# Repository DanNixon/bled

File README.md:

<h1 align="center">BLED</h1>

<p align="center">
  Versatile control board for WS2812 compatible LED fixtures.
  Using WebAssembly for effects and Bluetooth Low Energy for control.
</p>

---

**BLED is a work in progress.** Although mostly feature complete, specifics of the effect API are subject to change.
The web UI is likely to undergo significant changes, the current version is a mostly vibe coded prototype.

Documentation can be found in [`docs/README.md`](docs/README.md).

## Building effects

[`bled-effect`](lib/effect/README.md) is a helper library for building BLED effects in Rust and compiling them to WebAssembly. The [`effects`](effects) directory contains example effect crates.

## License

The project is licensed under the MIT License, see [`LICENSE.txt`](LICENSE.txt).

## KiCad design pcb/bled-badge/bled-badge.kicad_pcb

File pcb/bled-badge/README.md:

# Badge LED panel

A badge sized LED panel that takes a [BLED Stamp](../bled-stamp).

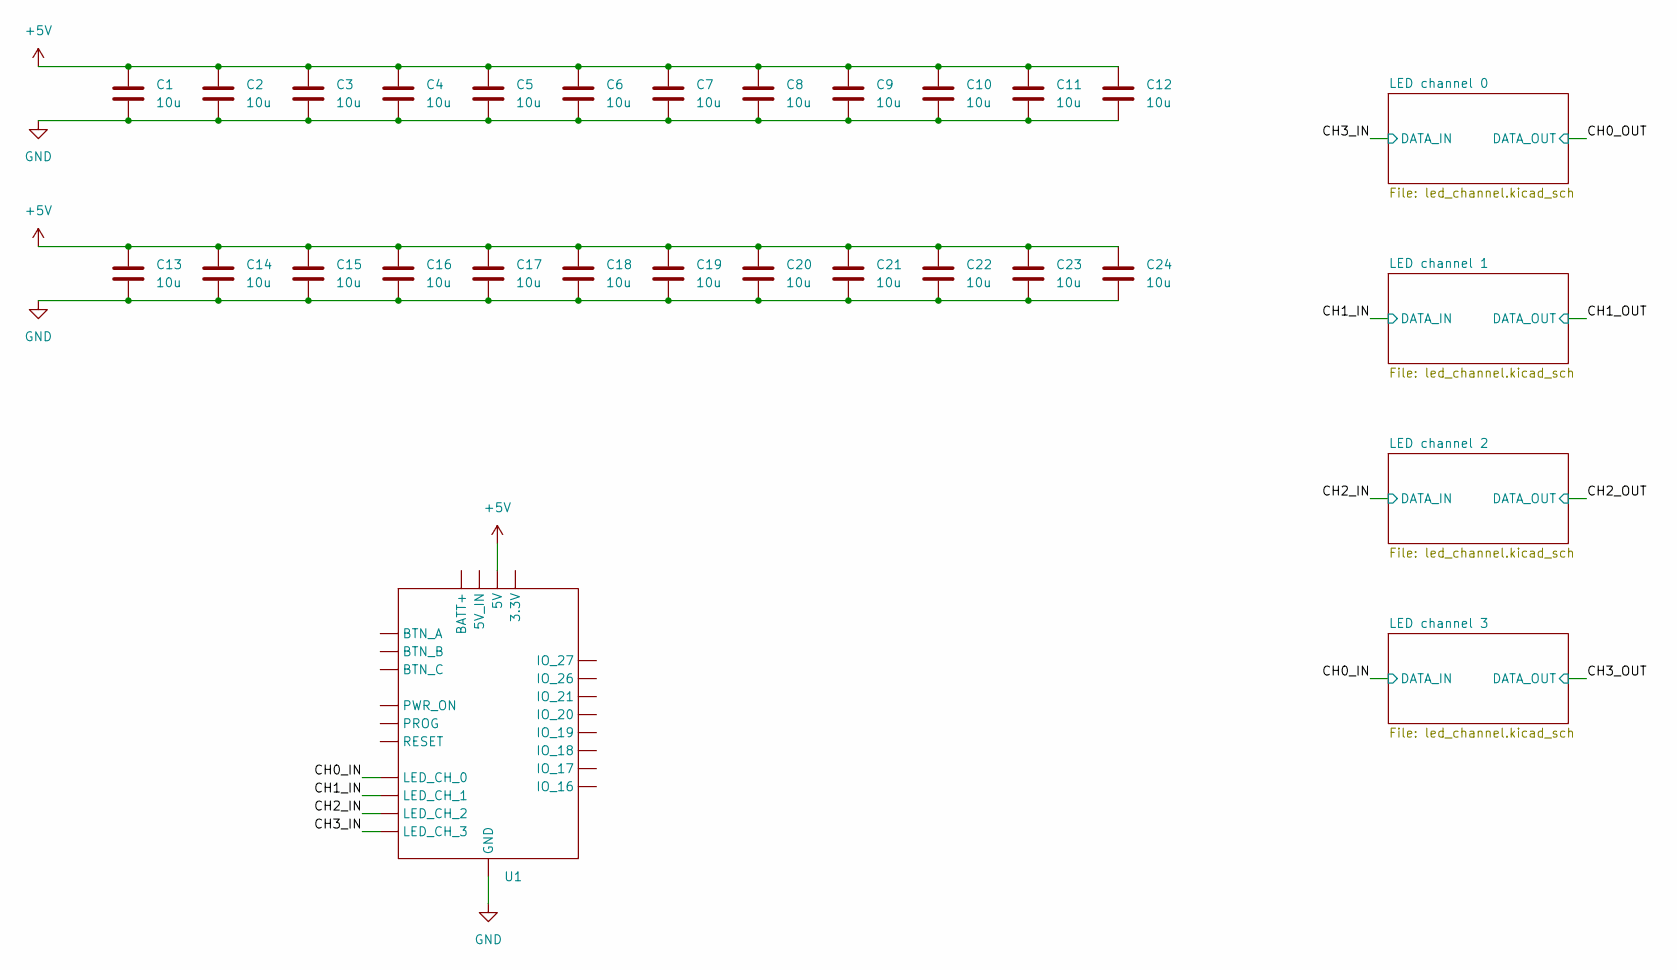
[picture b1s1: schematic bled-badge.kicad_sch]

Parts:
C1, C2, C3, C4, C5, C6, C7, C8, C9, C10, C11, C12, C13, C14, C15, C16, C17, C18, C19, C20, C21, C22, C23, C24: 10u; C_0402_1005Metric; LCSC C15525
U1: BLED_Stamp

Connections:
+5V: C1.1, C2.1, C3.1, C4.1, C5.1, C6.1, C7.1, C8.1, C9.1, C10.1, C11.1, C12.1, C13.1, C14.1, C15.1, C16.1, C17.1, C18.1, C19.1, C20.1, C21.1, C22.1, C23.1, C24.1, U1.6 (5V), U1.7 (5V), U1.8 (5V); also elsewhere on the board
/CH0_IN: U1.9 (LED_CH_0); also elsewhere on the board
/CH1_IN: U1.10 (LED_CH_1); also elsewhere on the board
/CH2_IN: U1.11 (LED_CH_2); also elsewhere on the board
/CH3_IN: U1.12 (LED_CH_3); also elsewhere on the board
GND: C1.2, C2.2, C3.2, C4.2, C5.2, C6.2, C7.2, C8.2, C9.2, C10.2, C11.2, C12.2, C13.2, C14.2, C15.2, C16.2, C17.2, C18.2, C19.2, C20.2, C21.2, C22.2, C23.2, C24.2, U1.1 (GND), U1.13 (GND), U1.14 (GND), U1.15 (GND), U1.16 (GND), U1.30 (GND); also elsewhere on the board
